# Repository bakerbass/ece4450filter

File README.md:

# ECE 4450 Final Project

This project is to create a functioning circuit on a Audible Waves form-factor module.

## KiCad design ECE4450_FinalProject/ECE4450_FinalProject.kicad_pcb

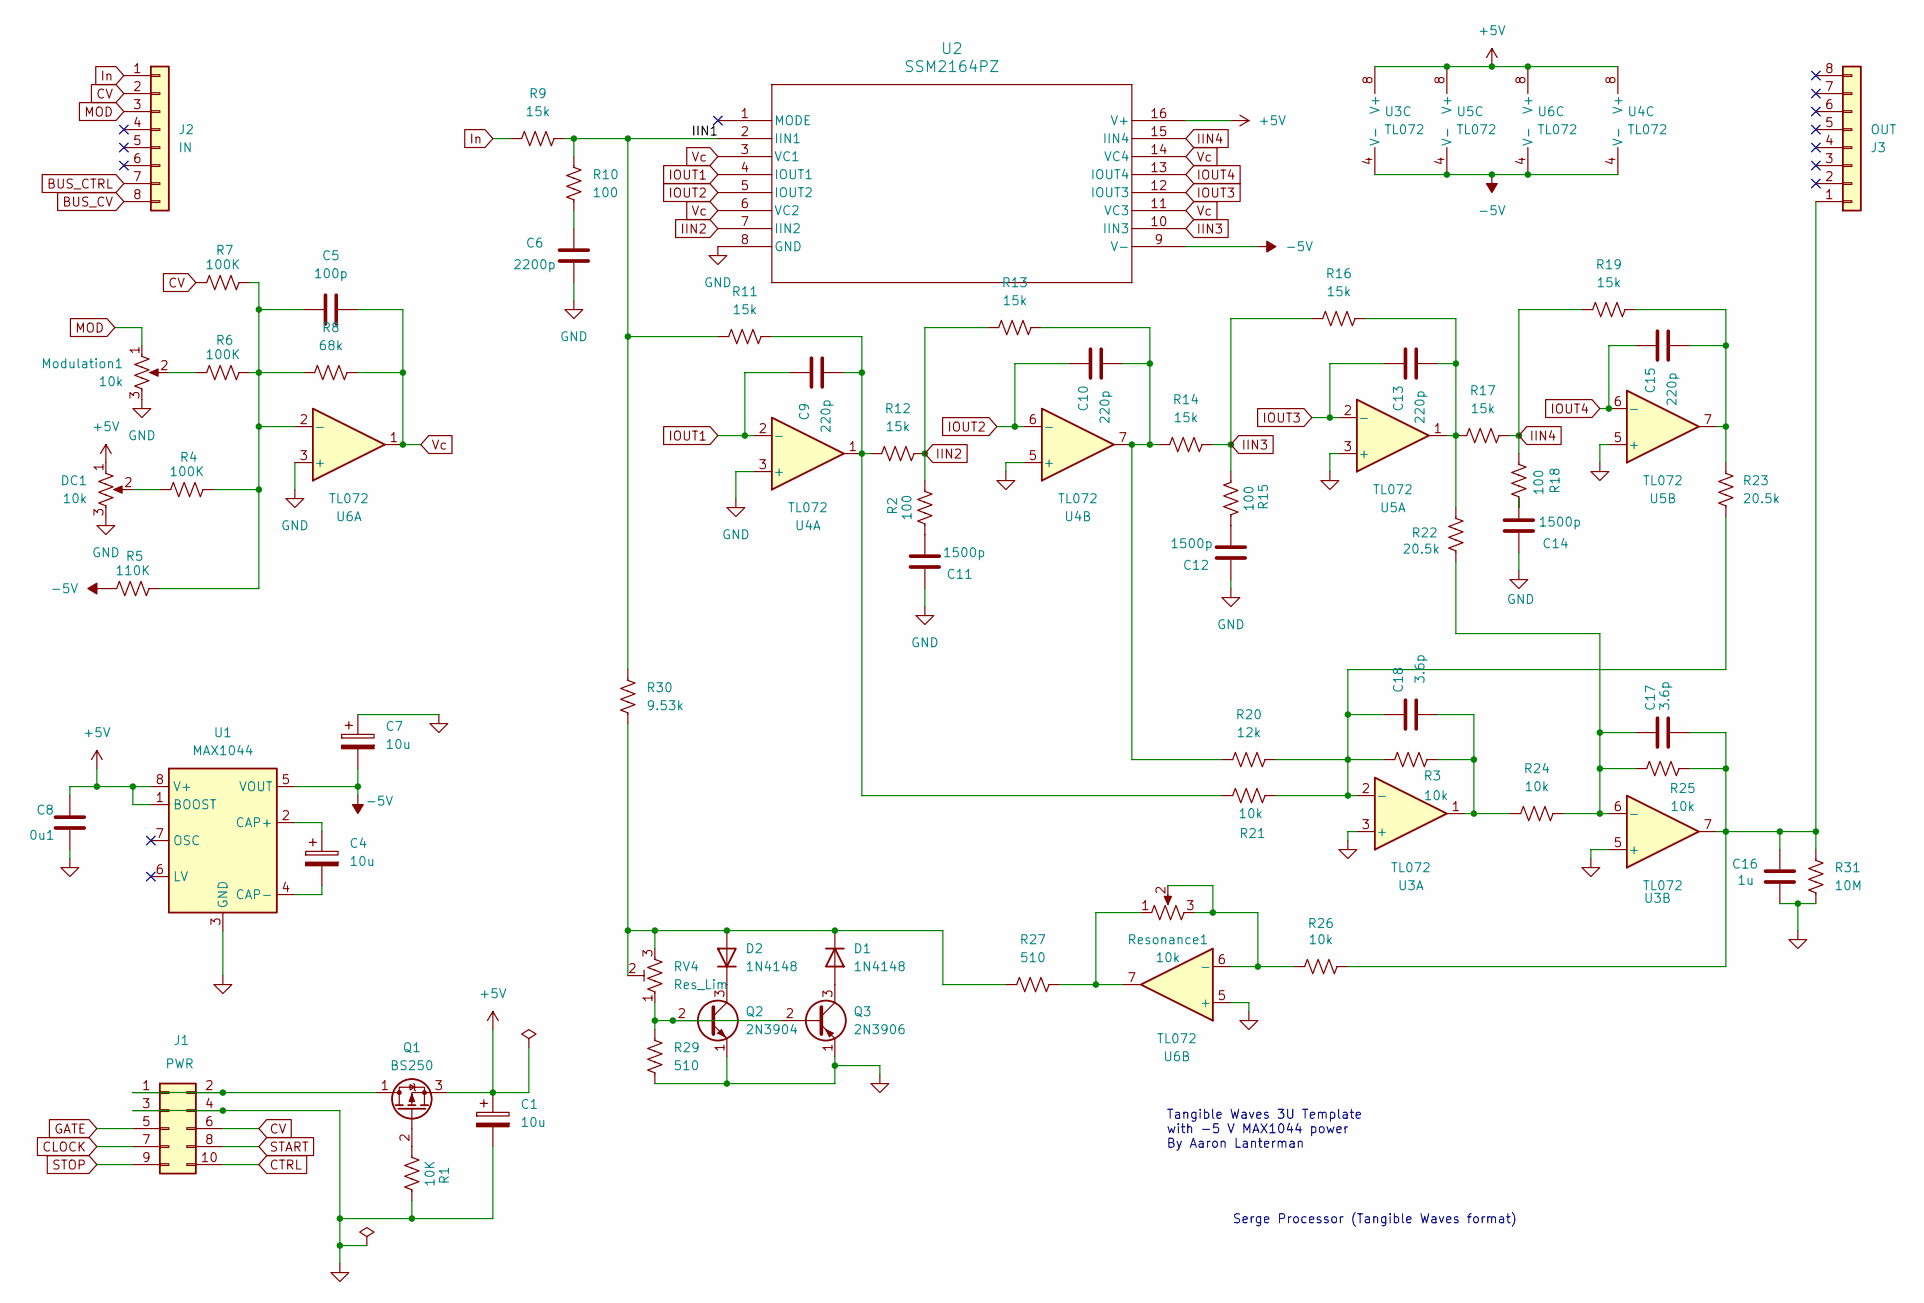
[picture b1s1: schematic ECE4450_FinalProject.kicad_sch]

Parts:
C1, C4, C7: 10u; CP_Radial_D5.0mm_P2.50mm
C5: 100p; C_Axial_Aaron
C6: 2200p; C_Axial_Aaron
C8: 0u1; C_Axial_Aaron
C9, C10, C13, C15: 220p; C_Axial_Aaron
C11, C12, C14: 1500p; C_Axial_Aaron
C16: 1u; C_Axial_Aaron
C17, C18: 3.6p; C_Axial_Aaron
D1, D2: 1N4148; D_DO-35_SOD27_P7.62mm_Horizontal
DC1: 10k; Potentiometer_TW_Frontpanel
J1: PWR; PinHeader_2x05_P2.54mm_Vertical
J2: IN; PinSocket_1x08_P2.54mm_Vertical
J3: OUT; PinSocket_1x08_P2.54mm_Vertical
Modulation1: 10k; Potentiometer_TW_Frontpanel
Q1: BS250; TO-92_Inline
Q2: 2N3904; TO-92_Inline
Q3: 2N3906; TO-92_Inline
R1: 10K; R_Axial_Aaron
R2, R10, R15, R18: 100; R_Axial_Aaron
R3, R21, R24, R25, R26: 10k; R_Axial_Aaron
R4, R6, R7: 100K; R_Axial_Aaron
R5: 110K; R_Axial_Aaron
R8: 68k; R_Axial_Aaron
R9, R11, R12, R13, R14, R16, R17, R19: 15k; R_Axial_Aaron
R20: 12k; R_Axial_Aaron
R22, R23: 20.5k; R_Axial_Aaron
R27, R29: 510; R_Axial_Aaron
R30: 9.53k; R_Axial_Aaron
R31: 10M; R_Axial_Aaron
RV4: Res_Lim; Potentiometer_Square_Trimpot_Aaron
Resonance1: 10k; Potentiometer_TW_Frontpanel
U1: MAX1044; DIP-8_W7.62mm
U2: SSM2164PZ; N_16_ADI
U3, U4, U5, U6: TL072; P8

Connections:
+5V: C1.1, C8.1, DC1.1, Q1.3 (S), U1.1 (BOOST), U1.8 (V+), U2.16 (V+), U3.8 (V+), U4.8 (V+), U5.8 (V+), U6.8 (V+)
-5V: C7.2, R5.2, U1.5 (VOUT), U2.9 (V-), U3.4 (V-), U4.4 (V-), U5.4 (V-), U6.4 (V-)
/IIN1: R9.2, R10.2, R11.1, R30.2, U2.2 (IIN1)
BUS_CTRL: J2.7
BUS_CV: J2.8
CLOCK: J1.7
CTRL: J1.10
CV: J1.6, J2.2, R7.2
GATE: J1.5
GND: C1.2, C6.1, C7.1, C8.2, C11.2, C12.2, C14.2, C16.1, DC1.3, J1.3, J1.4, Modulation1.3, Q2.1 (E), Q3.1 (E), R1.1, R29.1, R31.1, U1.3 (GND), U2.8 (GND), U3.3 (+), U3.5 (+), U4.3 (+), U4.5 (+), U5.3 (+), U5.5 (+), U6.3 (+), U6.5 (+)
IIN2: R2.1, R12.2, R13.1, U2.7 (IIN2)
IIN3: R14.2, R15.1, R16.1, U2.10 (IIN3)
IIN4: R17.2, R18.1, R19.2, U2.15 (IIN4)
IOUT1: C9.2, U2.4 (IOUT1), U4.2 (-)
IOUT2: C10.2, U2.5 (IOUT2), U4.6 (-)
IOUT3: C13.2, U2.12 (IOUT3), U5.2 (-)
IOUT4: C15.2, U2.13 (IOUT4), U5.6 (-)
In: J2.1, R9.1
MOD: J2.3, Modulation1.1
unnamed: C6.2, R10.1
unnamed: C9.1, R11.2, R12.1, R21.1, U4.1
unnamed: C10.1, R13.2, R14.1, R20.1, U4.7
unnamed: C11.1, R2.2
unnamed: C12.1, R15.2
unnamed: C13.1, R16.2, R17.1, R22.1, U5.1
unnamed: C14.1, R18.2
unnamed: C15.1, R19.1, R23.1, U5.7
unnamed: C18.1, R3.2, R24.1, U3.1
unnamed: D1.2 (A), Q3.3 (C)
unnamed: D1.1 (K), D2.2 (A), R27.1, R30.1, RV4.2, RV4.3
unnamed: D2.1 (K), Q2.3 (C)
unnamed: DC1.2, R4.2
unnamed: J1.1, J1.2, Q1.1 (D)
unnamed: C16.2, C17.1, J3.1, R25.2, R26.2, R31.2, U3.7
unnamed: Modulation1.2, R6.2
unnamed: Q1.2 (G), R1.2
unnamed: Q2.2 (B), Q3.2 (B), R29.2, RV4.1
unnamed: R27.2, Resonance1.1, U6.7
unnamed: C4.1, U1.2 (CAP+)
unnamed: C4.2, U1.4 (CAP-)
unnamed: C18.2, R3.1, R20.2, R21.2, R23.2, U3.2 (-)
unnamed: C17.2, R22.2, R24.2, R25.1, U3.6 (-)
unnamed: C5.1, R4.1, R5.1, R6.1, R7.1, R8.1, U6.2 (-)
unnamed: R26.1, Resonance1.2, Resonance1.3, U6.6 (-)
START: J1.8
STOP: J1.9
Vc: C5.2, R8.2, U2.3 (VC1), U2.6 (VC2), U2.11 (VC3), U2.14 (VC4), U6.1

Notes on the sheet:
Serge Processor (Tangible Waves format)
Tangible Waves 3U Template with -5 V MAX1044 power By Aaron Lanterman

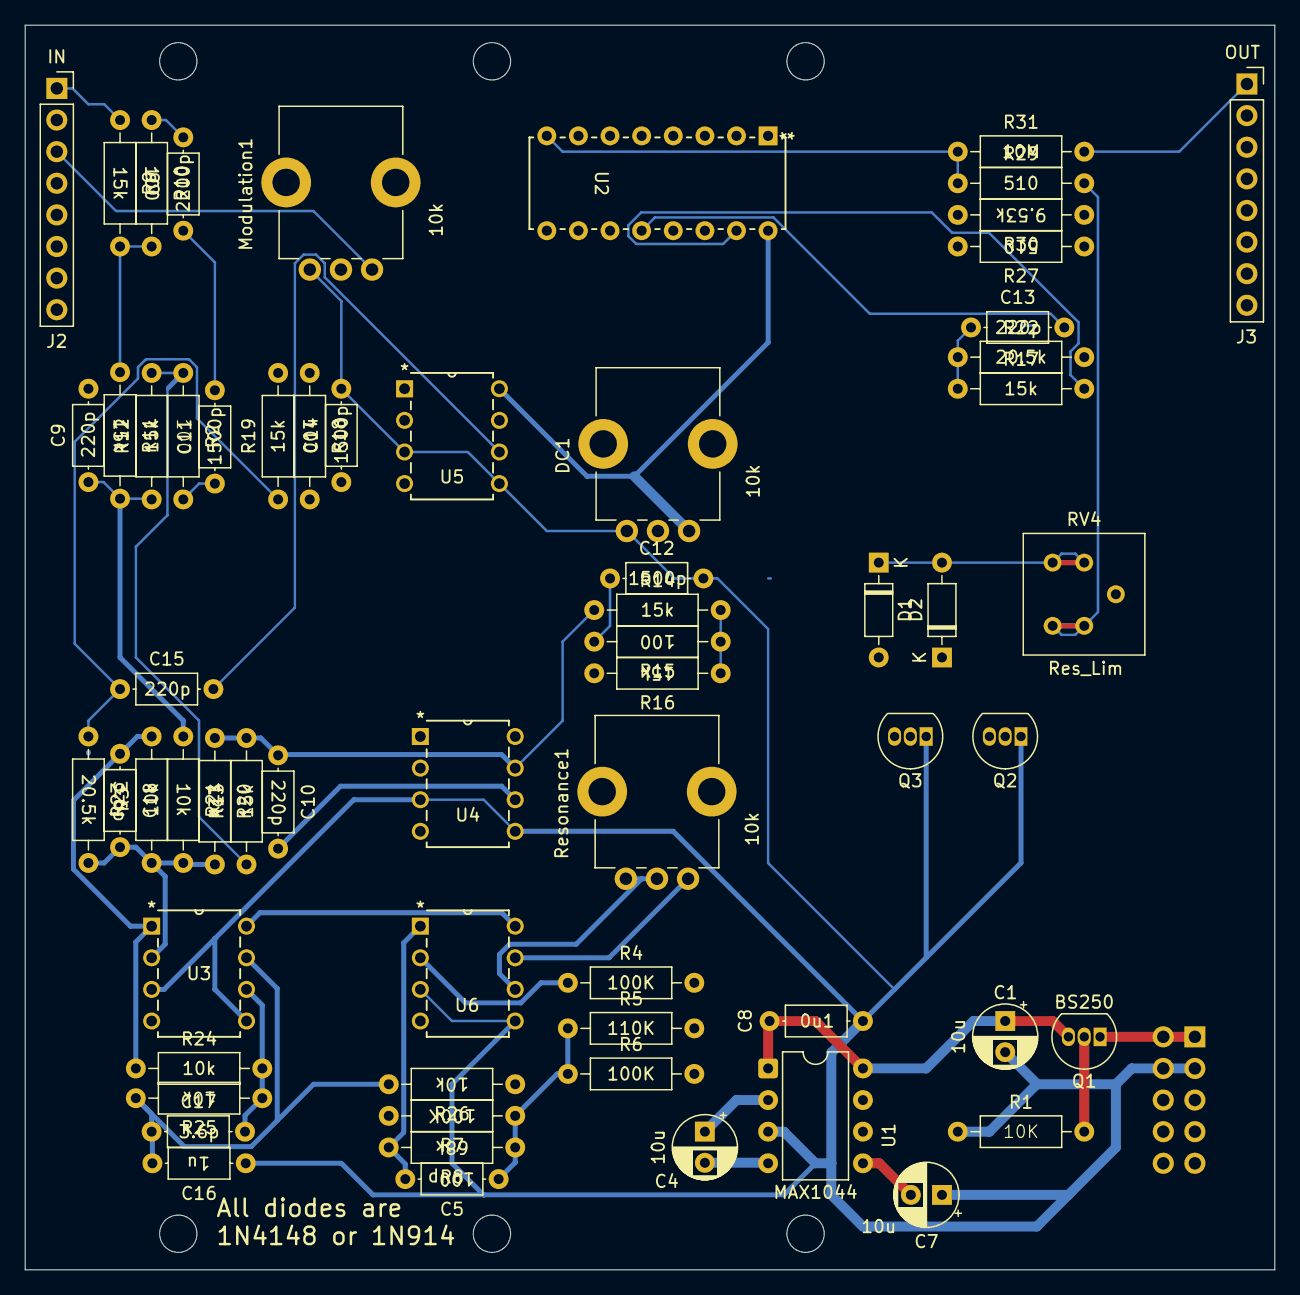
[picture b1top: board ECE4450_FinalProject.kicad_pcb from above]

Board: 2 copper layers, 100.4 x 100.0 mm, 64 parts (1 on the bottom side), 40 nets.

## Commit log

2025-04-02 init
2025-04-02 Commit test
2025-04-16 Fixed ERC, added footprints to components
2025-04-18 layout and single trace lacer
